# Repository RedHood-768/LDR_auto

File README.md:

# LDR_auto
LDR based automatic lighting system, operates on coin cell, tunable sensitivity of the LDR as well
Components Used :-
(i)-Coin Cell Holder:BAT_BLP2032SM-GTR
(ii)-LED_SMD:LED_0603_1608Metric.
(iii)-MountingHole:MountingHole_2.2mm_M2_Pad_Via(x3)
(iv)-Package_TO_SOT_THT:TO-92_Inline
(v)-OptoDevice:R_LDR_10x8.5mm_P7.6mm_Vertical
(vi)-trim potentiometer:TRIM_3362P-1-204.

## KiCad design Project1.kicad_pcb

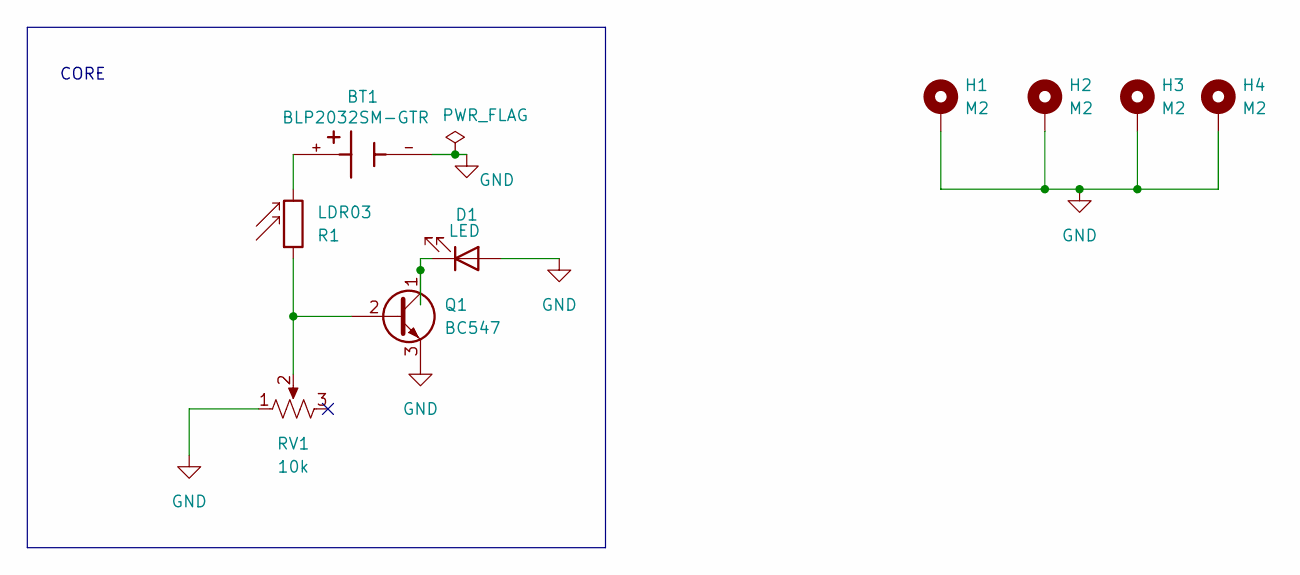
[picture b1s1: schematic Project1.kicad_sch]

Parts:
BT1: BLP2032SM-GTR; BAT_BLP2032SM-GTR; PARTREV J
D1: LED; LED_0603_1608Metric
H1, H2, H3, H4: M2; MountingHole_2.2mm_M2_Pad_Via
Q1: BC547; TO-92_Inline
R1: LDR03; R_LDR_10x8.5mm_P7.6mm_Vertical
RV1: 10k; TRIM_3362P-1-204

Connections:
GND: BT1.-, D1.2 (A), H1.1, H2.1, H3.1, H4.1, Q1.3 (E), RV1.1
unnamed: BT1.+, R1.2
unnamed: D1.1 (K), Q1.1 (C)
unnamed: Q1.2 (B), R1.1, RV1.2

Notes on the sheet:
CORE

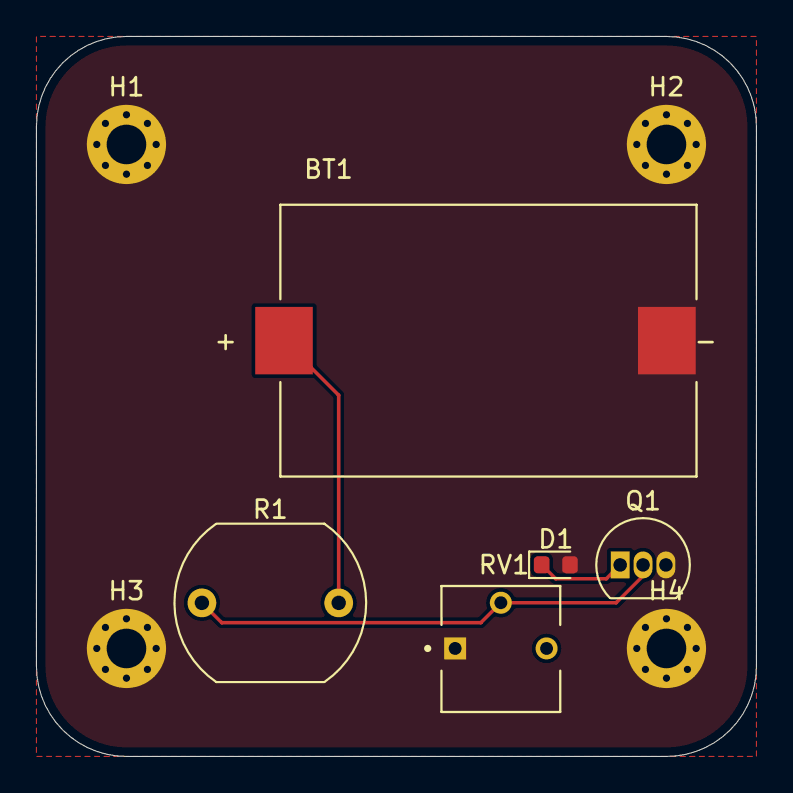
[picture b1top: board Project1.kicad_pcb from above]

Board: 2 copper layers, 40.0 x 40.0 mm, 9 parts (0 on the bottom side), 4 nets.

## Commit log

2024-09-29 Components.md
